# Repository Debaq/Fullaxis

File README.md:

# Fullaxis: Sistema de Evaluación Neurootológica

Fullaxis es un sistema diseñado para la evaluación neurootológica, proporcionando una interfaz gráfica intuitiva y herramientas de análisis de datos.

## Características

- **Interfaz Moderna**: Desarrollado con PySide5, Fullaxis ofrece una experiencia de usuario fluida y moderna.
- **Análisis de Datos**: Con herramientas como PyQtGraph y Numpy, el sistema proporciona análisis de datos en tiempo real.
- **Exportación de Datos**: Exporta tus datos a diferentes formatos para un análisis más detallado.
- **Módulos Integrados**:
  - **VNG (Video Nistagmografía)**: Utiliza el equipo de [ocular_tracking](https://github.com/Debaq/ocular_tracking).
  - **Timed Up and Go (TUG)**: Implementado con el equipo [PosturalAxis](https://github.com/Debaq/PosturalAxis).

## Instalación

Para instalar y ejecutar Fullaxis, sigue los siguientes pasos:

1. Clona el repositorio:
   ```bash
   git clone https://github.com/debaq/Fullaxis.git
   cd Fullaxis
   ```

2. Instala las dependencias:
   ```bash
   pip install -r requirements.txt
   ```

3. Ejecuta el programa:
   ```bash
   fbs run
   ```

## Dependencias

- [PySide5](https://pypi.org/project/PySide5/)
- [PyQtGraph](https://pypi.org/project/pyqtgraph/)
- [Numpy](https://pypi.org/project/numpy/)
- [fbs](https://pypi.org/project/fbs/)
- [qtawesome](https://pypi.org/project/qtawesome/)
- [Pandas](https://pypi.org/project/pandas/)
- [ezodf](https://pypi.org/project/ezodf/)
- [PeakUtils](https://pypi.org/project/PeakUtils/)

## Contribuciones

Las contribuciones son bienvenidas. Si encuentras algún error o tienes alguna sugerencia, no dudes en abrir un issue o enviar un pull request.

## Créditos

- **Nicolás Quezada Baier** (David Ávila Quezada)

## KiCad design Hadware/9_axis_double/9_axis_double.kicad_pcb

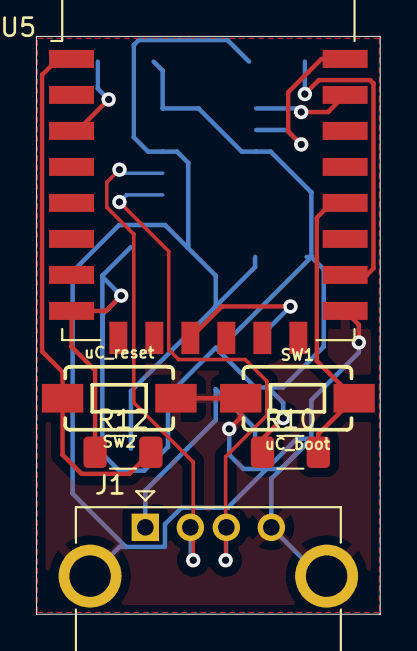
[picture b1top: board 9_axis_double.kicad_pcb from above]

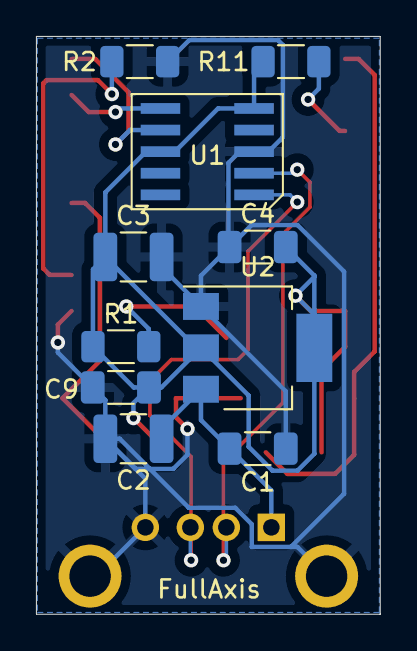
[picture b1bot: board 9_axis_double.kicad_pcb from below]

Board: 2 copper layers, 19.1 x 32.1 mm, 16 parts (10 on the bottom side), 12 nets.

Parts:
C1, C4: 22nF; C_1206_3216Metric_Pad1.33x1.80mm_HandSolder
C2, C3: 100nF; C_1210_3225Metric_Pad1.33x2.70mm_HandSolder
C9: 100nF; C_1206_3216Metric_Pad1.33x1.80mm_HandSolder
J1: USB_A; USB_A_CONNFLY_DS1095-WNR0
R1, R2, R11: 10K; R_1206_3216Metric_Pad1.30x1.75mm_HandSolder
R10, R12: 10k; R_1206_3216Metric_Pad1.30x1.75mm_HandSolder
SW1: uC_boot; TACTILE_SWITCH_SMD_6.0X3.5MM
SW2: uC_reset; TACTILE_SWITCH_SMD_6.0X3.5MM
U1: ch340n; SOIC-10
U2: AMS1117-3.3; SOT-223-3_TabPin2
U5: ESP-12F; ESP-12E

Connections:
+3V3: C3.1, C4.2, C9.1, R1.1, R10.1, R11.1, R12.1, U1.5 (VCC), U1.8 (V3), U2.2 (VO), U5.8 (VCC)
+5V: C1.2, C2.1, J1.1 (VBUS), U2.3 (VI)
D+: J1.3 (D+), U1.1 (UD+)
D-: J1.2 (D-), U1.2 (UD-)
GND: C1.1, C2.2, C3.2, C4.1, C9.2, J1.4 (GND), J1.5 (Shield), R2.2, SW1.1, SW2.1, U1.3 (GND), U2.1 (GND), U5.15 (GND)
unnamed: R1.2, U5.11 (GPIO9)
unnamed: R2.1, U5.16 (GPIO15)
unnamed: R11.2, U5.3 (EN)
uC_RX: U1.6 (TXD), U5.21 (GPIO3/RXD)
uC_TX: U1.7 (RXD), U5.22 (GPIO1/TXD)
uC_boot: R10.2, SW1.2, U5.18 (GPIO0)
uC_reset: R12.2, SW2.2, U5.1 (~RST)

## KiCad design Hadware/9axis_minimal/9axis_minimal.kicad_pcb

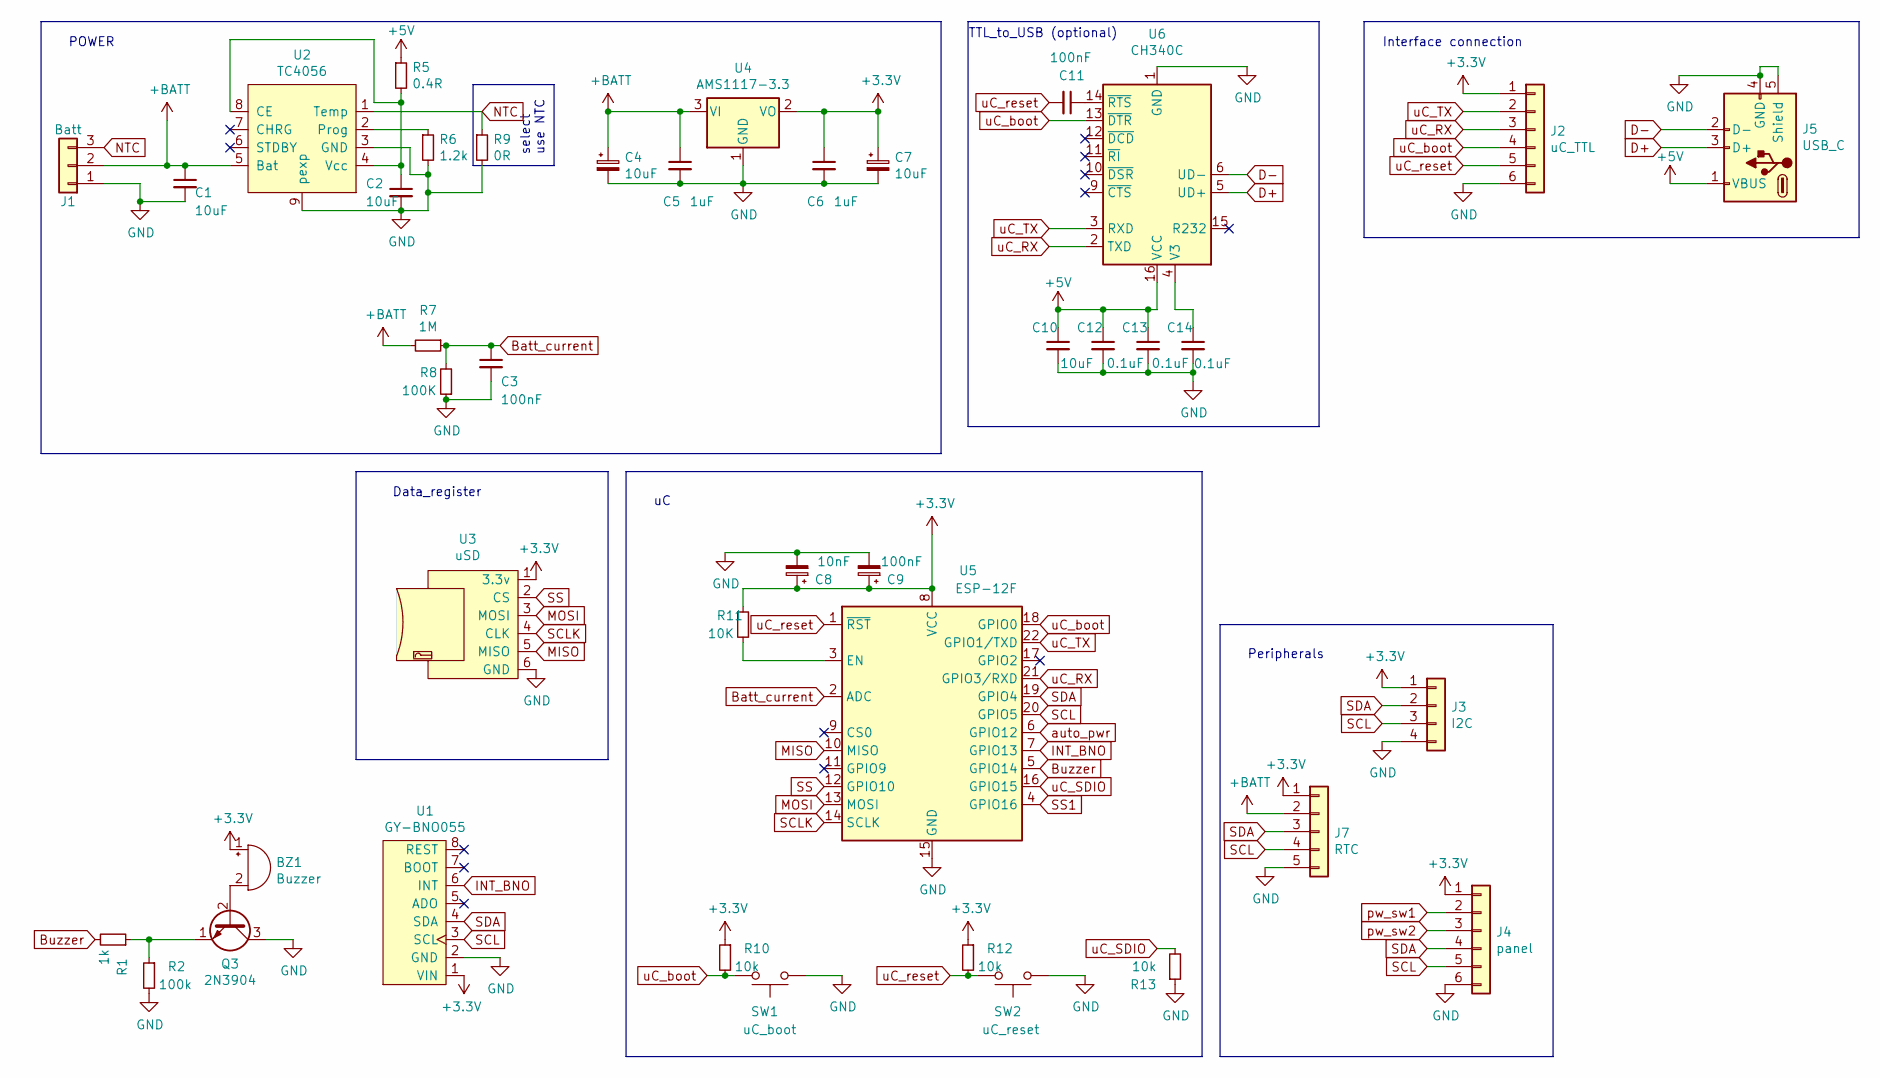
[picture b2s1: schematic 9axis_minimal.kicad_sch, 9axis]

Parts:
BZ1: Buzzer; MagneticBuzzer_PUI_AT-0927-TT-6-R
C1, C2, C4, C7, C10: 10uF; C_1206_3216Metric_Pad1.33x1.80mm_HandSolder
C3, C9, C11: 100nF; C_1206_3216Metric_Pad1.33x1.80mm_HandSolder
C5, C6: 1uF; C_1206_3216Metric_Pad1.33x1.80mm_HandSolder
C8: 10nF; C_1206_3216Metric_Pad1.33x1.80mm_HandSolder
C12, C13, C14: 0.1uF; C_1206_3216Metric_Pad1.33x1.80mm_HandSolder
J1: Batt; JST_GH_BM03B-GHS-TBT_1x03-1MP_P1.25mm_Vertical
J2: uC_TTL; JST_GH_BM06B-GHS-TBT_1x06-1MP_P1.25mm_Vertical
J3: I2C; JST_GH_BM04B-GHS-TBT_1x04-1MP_P1.25mm_Vertical
J4: panel; JST_GH_BM06B-GHS-TBT_1x06-1MP_P1.25mm_Vertical
J5: USB_C; JST_GH_BM05B-GHS-TBT_1x05-1MP_P1.25mm_Vertical
J7: RTC; JST_GH_BM05B-GHS-TBT_1x05-1MP_P1.25mm_Vertical
Q3: 2N3904; TO-92_Inline
R1: 1k; R_1206_3216Metric_Pad1.30x1.75mm_HandSolder
R2: 100k; R_1206_3216Metric_Pad1.30x1.75mm_HandSolder
R5: 0.4R; R_1206_3216Metric_Pad1.30x1.75mm_HandSolder
R6: 1.2k; R_1206_3216Metric_Pad1.30x1.75mm_HandSolder
R7: 1M; R_1206_3216Metric_Pad1.30x1.75mm_HandSolder
R8: 100K; R_1206_3216Metric_Pad1.30x1.75mm_HandSolder
R9: 0R; R_1206_3216Metric_Pad1.30x1.75mm_HandSolder
R10, R12, R13: 10k; R_1206_3216Metric_Pad1.30x1.75mm_HandSolder
R11: 10K; R_1206_3216Metric_Pad1.30x1.75mm_HandSolder
SW1: uC_boot; TACTILE_SWITCH_SMD_6.0X3.5MM
SW2: uC_reset; TACTILE_SWITCH_SMD_6.0X3.5MM
U1: GY-BNO055; PinSocket_1x08_P2.54mm_Horizontal
U2: TC4056
U3: uSD; JST_GH_BM06B-GHS-TBT_1x06-1MP_P1.25mm_Vertical
U4: AMS1117-3.3; SOT-223-3_TabPin2
U5: ESP-12F; ESP-12E
U6: CH340C; SOIC-16_3.9x9.9mm_P1.27mm

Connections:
+3V3: BZ1.1 (-), C6.1, C7.1, C8.1, C9.1, J2.1, J3.1, J4.1, J7.1, R10.1, R11.1, R12.1, U1.1 (VIN), U3.1 (3.3v), U4.2 (VO), U5.8 (VCC)
+5V: C10.1, C12.1, C13.1, J5.1 (VBUS), R5.1, U6.16 (VCC)
+BATT: C1.1, C4.1, C5.1, J1.2, J7.2, R7.2, U2.5 (Bat), U4.3 (VI)
Batt_current: C3.1, R7.1, R8.2, U5.2 (ADC)
Buzzer: R1.2, U5.5 (GPIO14)
D+: J5.3 (D+), U6.5 (UD+)
D-: J5.2 (D-), U6.6 (UD-)
GND: C1.2, C2.2, C3.2, C4.2, C5.2, C6.2, C7.2, C8.2, C9.2, C10.2, C12.2, C13.2, C14.2, J1.1, J2.6, J3.4, J4.6, J5.4 (GND), J5.5 (Shield), J7.5, Q3.3 (C), R2.2, R6.2, R8.1, R9.2, R13.1, SW1.1, SW2.1, U1.2 (GND), U2.3 (GND), U2.9 (pexp), U3.6 (GND), U4.1 (GND), U5.15 (GND), U6.1 (GND)
INT_BNO: U1.6 (INT), U5.7 (GPIO13)
MISO: U3.5 (MISO), U5.10 (MISO)
MOSI: U3.3 (MOSI), U5.13 (MOSI)
NTC: J1.3, R9.1, U2.1 (Temp)
unnamed: BZ1.2 (+), Q3.2 (B)
unnamed: C2.1, R5.2, U2.4 (Vcc), U2.8 (CE)
unnamed: C11.1, U6.14 (~RTS)
unnamed: C14.1, U6.4 (V3)
unnamed: Q3.1 (E), R1.1, R2.1
unnamed: R6.1, U2.2 (Prog)
unnamed: R11.2, U5.3 (EN)
SCL: J3.3, J4.5, J7.4, U1.3 (SCL), U5.20 (GPIO5)
SCLK: U3.4 (CLK), U5.14 (SCLK)
SDA: J3.2, J4.4, J7.3, U1.4 (SDA), U5.19 (GPIO4)
SS: U3.2 (CS), U5.12 (GPIO10)
SS1: U5.4 (GPIO16)
auto_pwr: U5.6 (GPIO12)
pw_sw1: J4.2
pw_sw2: J4.3
uC_RX: J2.3, U5.21 (GPIO3/RXD), U6.2 (TXD)
uC_SDIO: R13.2, U5.16 (GPIO15)
uC_TX: J2.2, U5.22 (GPIO1/TXD), U6.3 (RXD)
uC_boot: J2.4, R10.2, SW1.2, U5.18 (GPIO0), U6.13 (~DTR)
uC_reset: C11.2, J2.5, R12.2, SW2.2, U5.1 (~RST)

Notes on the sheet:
Data_register
TTL_to_USB (optional)
Interface connection
POWER
Peripherals
select use NTC

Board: 2 copper layers, 38 parts (0 on the bottom side), 27 nets, no tracks yet.

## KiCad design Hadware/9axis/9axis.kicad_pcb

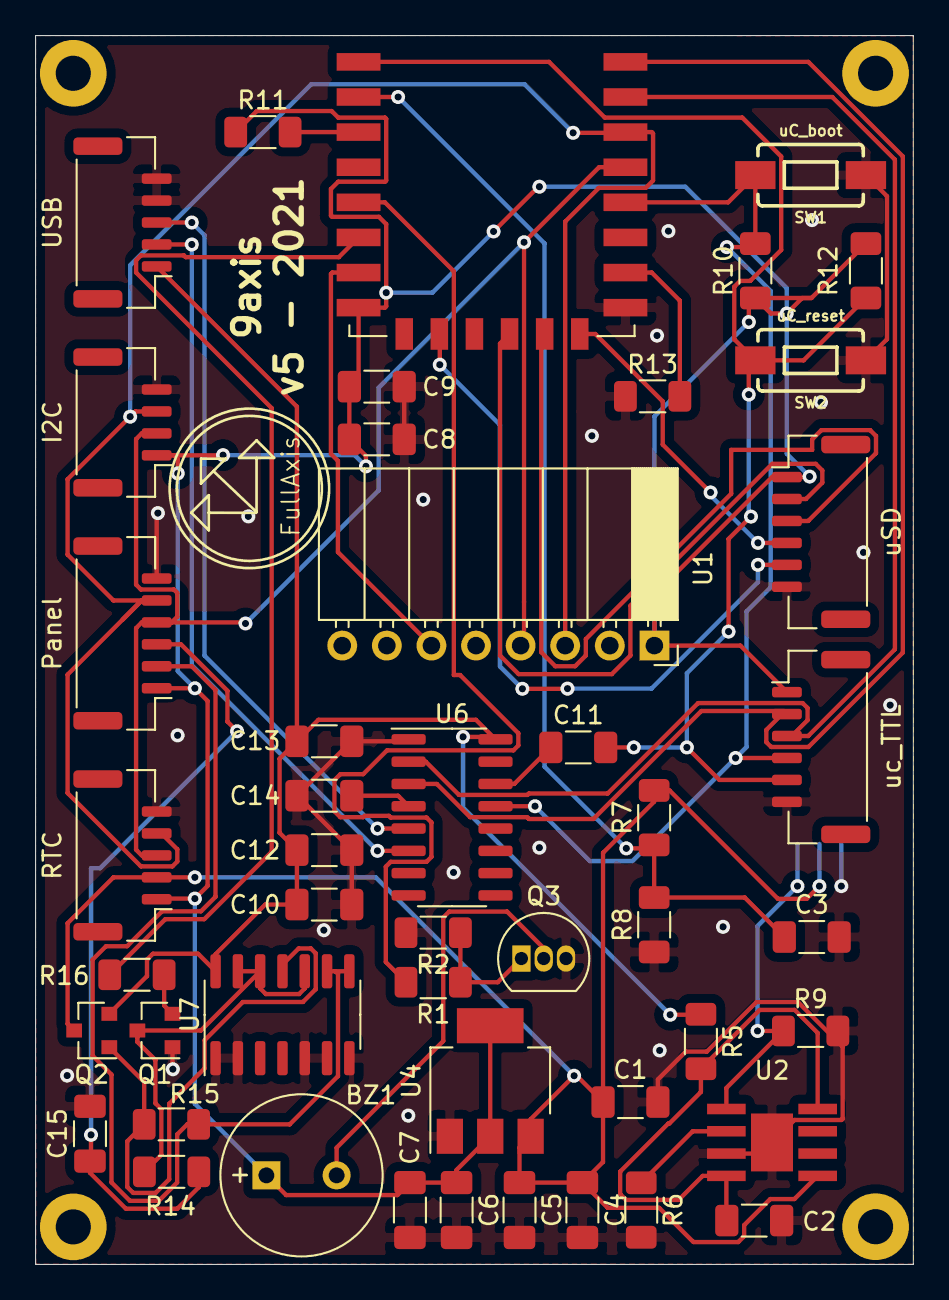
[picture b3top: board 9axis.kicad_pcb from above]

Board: 2 copper layers, 50.0 x 70.0 mm, 48 parts (1 on the bottom side), 34 nets.

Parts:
BZ1: Buzzer; MagneticBuzzer_PUI_AT-0927-TT-6-R
Batt: Batt; JST_GH_BM03B-GHS-TBT_1x03-1MP_P1.25mm_Vertical
C1, C2, C4, C7, C10: 10uF; C_1206_3216Metric_Pad1.33x1.80mm_HandSolder
C3, C9, C11: 100nF; C_1206_3216Metric_Pad1.33x1.80mm_HandSolder
C5, C6: 1uF; C_1206_3216Metric_Pad1.33x1.80mm_HandSolder
C8: 10nF; C_1206_3216Metric_Pad1.33x1.80mm_HandSolder
C12, C13, C14, C15: 0.1uF; C_1206_3216Metric_Pad1.33x1.80mm_HandSolder
I2C: I2C; JST_GH_BM04B-GHS-TBT_1x04-1MP_P1.25mm_Vertical
Panel: panel; JST_GH_BM06B-GHS-TBT_1x06-1MP_P1.25mm_Vertical
Q1: PN2222A; SOT-23
Q2: IRLML6402; SOT-23
Q3: 2N3904; TO-92_Inline
R1, R16: 1k; R_1206_3216Metric_Pad1.30x1.75mm_HandSolder
R2, R14, R15: 100k; R_1206_3216Metric_Pad1.30x1.75mm_HandSolder
R5: 0.4R; R_1206_3216Metric_Pad1.30x1.75mm_HandSolder
R6: 1.2k; R_1206_3216Metric_Pad1.30x1.75mm_HandSolder
R7: 1M; R_1206_3216Metric_Pad1.30x1.75mm_HandSolder
R8: 100K; R_1206_3216Metric_Pad1.30x1.75mm_HandSolder
R9: 0R; R_1206_3216Metric_Pad1.30x1.75mm_HandSolder
R10, R12, R13: 10k; R_1206_3216Metric_Pad1.30x1.75mm_HandSolder
R11: 10K; R_1206_3216Metric_Pad1.30x1.75mm_HandSolder
RTC: RTC; JST_GH_BM05B-GHS-TBT_1x05-1MP_P1.25mm_Vertical
SW1: uC_boot; TACTILE_SWITCH_SMD_6.0X3.5MM
SW2: uC_reset; TACTILE_SWITCH_SMD_6.0X3.5MM
U1: GY-BNO055; PinSocket_1x08_P2.54mm_Horizontal
U2: TC4056
U4: AMS1117-3.3; SOT-223-3_TabPin2
U5: ESP-12F; ESP-12E
U6: CH340C; SOIC-16_3.9x9.9mm_P1.27mm
U7: HEF4093BT; SO-14_3.9x8.65mm_P1.27mm
USB: USB_C; JST_GH_BM05B-GHS-TBT_1x05-1MP_P1.25mm_Vertical
uSD: uSD; JST_GH_BM06B-GHS-TBT_1x06-1MP_P1.25mm_Vertical
uc_TTL: uC_TTL; JST_GH_BM06B-GHS-TBT_1x06-1MP_P1.25mm_Vertical

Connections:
+3V3: BZ1.1, C6.1, C7.1, C8.1, C9.1, I2C.1, Panel.1, R10.1, R11.1, R12.1, RTC.1, U1.1, U4.2, U5.8, uSD.1, uc_TTL.1
+5V: C10.1, C12.1, C13.1, Q2.2, R5.1, U6.16, U7.14, USB.1
+BATT: Batt.2, C1.1, C4.1, C5.1, Q2.3, R7.2, RTC.2, U2.5, U4.3
Batt_current: C3.1, R7.1, R8.2, U5.2
Buzzer: R1.2, U5.5
D+: U6.5, USB.3
D-: U6.6, USB.2
GND: Batt.1, C1.2, C2.2, C3.2, C4.2, C5.2, C6.2, C7.2, C8.2, C9.2, C10.2, C12.2, C13.2, C14.2, C15.2, I2C.4, Panel.6, Q1.1, Q3.3, R2.2, R6.2, R8.1, R9.2, R13.1, RTC.5, SW1.1, SW2.1, U1.2, U2.3, U2.9, U4.1, U5.15, U6.1, U7.1, U7.2, U7.5, U7.6, U7.7, USB.4, USB.5, uSD.6, uc_TTL.6
INT_BNO: U1.6, U5.7
MISO: U5.10, uSD.5
MOSI: U5.13, uSD.3
NTC: Batt.3, R9.1, U2.1
unnamed: BZ1.2, Q3.2
unnamed: C2.1, R5.2, U2.4, U2.8
unnamed: C11.1, U6.14
unnamed: C14.1, U6.4
unnamed: Q1.2, R16.2
unnamed: Q1.3, R14.1, U7.10, U7.12, U7.13
unnamed: Q2.1, R15.1, U7.11
unnamed: Q3.1, R1.1, R2.1
unnamed: R6.1, U2.2
unnamed: R11.2, U5.3
SCL: I2C.3, Panel.5, RTC.4, U1.3, U5.20
SCLK: U5.14, uSD.4
SDA: I2C.2, Panel.4, RTC.3, U1.4, U5.19
SS: U5.12, uSD.2
auto_pwr: R16.1, U5.6
pw_sw1: Panel.2, R15.2, U7.8, U7.9
pw_sw2: C15.1, Panel.3, R14.2
uC_RX: U5.21, U6.2, uc_TTL.3
uC_SDIO: R13.2, U5.16
uC_TX: U5.22, U6.3, uc_TTL.2
uC_boot: R10.2, SW1.2, U5.18, U6.13, uc_TTL.4
uC_reset: C11.2, R12.2, SW2.2, U5.1, uc_TTL.5

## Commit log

2015-10-29 Commit message
2019-10-03 cambio de archivos
2019-10-03 cambios menores
2019-10-03 cambio de nombre carpeta
2019-10-03 cambio de carpeta
2019-10-04 modificaciones de carpeta
2019-10-04 se agregan imagenes
2019-10-04 se agregan autores
2019-10-04 cambio menores
2019-10-05 add images
2019-10-05 se agrega
2019-10-05 agradecimientos
2019-10-07 new test
2019-10-12 nueva carpeta
2019-10-13 se mueve carpeta y archivos
2019-10-14 imagnes nuevas
2019-12-06 Cambios Varios
2019-12-09 cambios mayores
2019-12-10 nuevos cambios
2019-12-11 muchos cambios
2020-06-17 eliminados archivos no blanqueados
2020-06-17 nueva versión v20.6
2020-06-17 se agrega notebook jupyter
2020-06-17 archivos de vscode
2020-06-17 se agrega api server
2020-06-17 gitignore
2020-06-17 se cambian propiedades gitignore
2020-06-17 eliminando lo de vscode
2020-06-17 cambios en gitignore
2020-06-17 cambio a 20.6
2020-06-17 Version 20.6-pre
2020-06-17 se elimina workspace
2020-06-17 conector y API servidor
2020-06-17 se agrega un alerta
2020-06-17 conector y api para b2
2020-06-18 cambios en API, ui, y login
2020-06-18 cambios en msg de error 060
2020-06-19 Funcionalidad hasta el logeo
2020-06-19 se eliminan metodos repetidos
2020-06-21 Se cambio a PyQT5
    Se cambio la dispocición del gui principal
    se agrego la posibilidad de cambiar de temas
    se puede logear y deslogear
2020-06-21 cambios en interfaz
2020-06-21 cambios a versión 20.6.1
2020-06-22 versión 20.6.21
2020-06-23 v20.6.22
2020-06-23 patch 23
2020-06-25 nuevos plugins
2020-06-28 cambios
2020-07-01 cambio en estilos
2020-07-01 widget
2020-07-03 graficador
2020-07-03 tiradores funcionales
2020-07-03 calcula la amplitud
2020-07-03 cool
2020-07-03 version 20.7.3
2020-07-04 orden en los tiradores
2020-07-04 desabilitado boton dee ingreso
2020-07-04 copiar linea
2020-07-04 se agrega funcion en boton clear_table
2020-07-04 boton copy all
2020-07-04 reparado el copyall
2020-07-05 preview
2020-07-07 mejoras
2020-07-07 herramientas grafico mejoradas
2020-07-07 se agregan iconos
2020-07-07 mejoras en el esquema
2020-07-10 nuevo
2020-07-24 v.20.7.24
2020-07-24 dependencias
2020-07-24 marcador de tiempo
2020-07-25 add compare
2020-07-25 compare update
2022-02-25 cambios a pyside6
2022-02-25 create fbs
2022-02-25 cambios_varios
2022-02-26 super_changes
2022-02-27 nueva_version
2022-02-28 cambios mayores
    se consiguio que graficara, aun hay problema de estabilidad se pega el software al registrar quizas hay que desconectar el serial
2022-02-28 sin logros significativos
2022-02-28 se elimina target
2022-02-28 pura ched
2022-02-28 cambios funcionales, varios
2022-03-02 cambios en windows
2022-03-03 cambios importantes
2022-03-03 problema con los iconos
2022-03-03 cambios funcionales
2022-03-04 cambios para compatibilidad en windows
2022-03-06 cambios varios
    guarda la prueba antes de presionar el boton de guardar (solucionado)
    se pega la conexion cuando se intenta tomar mas de una prueba
    no se pueden borrar las sesiones ni las pruebas
    no puede medir en los graficos de la vista de la prueba (solucionado)
    cambiar en el eje y amplitud por nombre de plano (solucionado)
    poner dibujo para los ejes
2022-03-06 nuew issuses
    guarda la prueba antes de presionar el boton de guardar (solucionado)
    se pega la conexion cuando se intenta tomar mas de una prueba
    existe un deley del buffer luego de los 5 segundos
    no se pueden borrar las sesiones(incompleto) ni las pruebas (solucionado)
    no puede medir en los graficos de la vista de la prueba (solucionado)
    cambiar en el eje y amplitud por nombre de plano (solucionado)
2022-03-07 corrección de varios issues
2022-03-07 issues mas dificil resuelto
2022-03-14 hardware
2022-04-22 cambios mejores
2022-04-23 cambios menores y reparaciones
2022-06-27 agregado vng
2022-06-28 se elimina VNG
2022-06-29 cambios de gui
2022-06-29 cambios en fullaxis
2022-07-10 cambios an ueva versión
2022-07-11 limpieza
2022-07-11 clean
2022-07-15 cambios?
2022-07-22 se ordenan clases de graficos
    se cambiaron el orden de los archivos en graph para una mejor comprensión
2022-07-25 cambios en ui
2022-08-15 'Refactored by Sourcery'
2023-06-22 cambio de versión
2023-06-22 punto de guardado
2023-06-24 cambios a nueva versión
2023-06-26 cambios para windows
2023-06-26 cambios para seleccion de camara automatica
2023-07-24 cambios nuevos
2023-08-20 readme
2023-10-19 cambios version 2
2023-11-11 cambios en el modulo vng
2023-11-14 cambios en funcionamiento y markage
    se agrega grafico
2023-11-24 ni idea
    ni idea
2023-11-29 cambio de camara
2024-03-04 cambios en v1
2024-03-15 cambios minimos
2024-03-15 cambios en el tick
2024-03-15 reparacion de emergencia
